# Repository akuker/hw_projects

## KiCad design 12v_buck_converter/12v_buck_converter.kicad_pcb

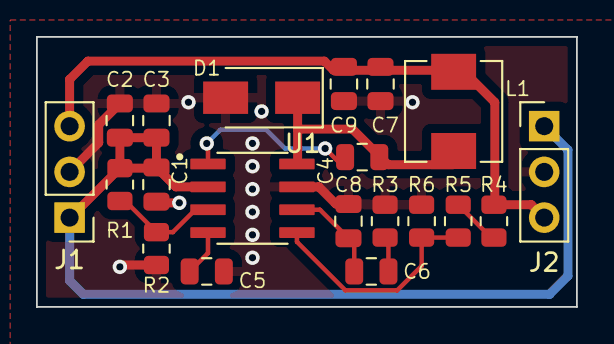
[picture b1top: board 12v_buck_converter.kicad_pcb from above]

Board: 2 copper layers, 30.0 x 15.0 mm, 20 parts (0 on the bottom side), 11 nets.

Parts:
C1, C2: 4.7u; C_0805_2012Metric
C3, C6: 4.7n; C_0805_2012Metric
C4: 0.1u; C_0805_2012Metric
C5: 0.01u; C_0805_2012Metric
C7, C9: 33u; C_0805_2012Metric
C8: 39p; C_0805_2012Metric
D1: B340A; D_SMA
J1, J2: Conn_01x03_Male; PinHeader_1x03_P2.54mm_Vertical
L1: 6.8uH; Sunltech_SLO0530H
R1: 332k; R_0805_2012Metric
R2: 68.1k; R_0805_2012Metric
R3: 49.9k; R_0805_2012Metric
R4: 0; R_0805_2012Metric
R5: 10.2k; R_0805_2012Metric
R6: 3.24k; R_0805_2012Metric
U1: TPS54331DR; SOIC127P599X175-8N

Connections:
+5V: C7.1, C9.1, J1.3, J2.3, L1.2, R4.1
+12V: C1.1, C2.1, C3.1, J1.1, J2.1, R1.1, U1.2 (VIN)
GND: C1.2, C2.2, C3.2, C5.2, C7.2, C8.2, C9.2, D1.2 (A), J1.2, J2.2, R2.2, R3.2, R6.2, U1.7 (GND)
unnamed: C4.1, D1.1 (K), L1.1, U1.8 (PH)
unnamed: C4.2, U1.1 (BOOT)
unnamed: C5.1, U1.4 (SS)
unnamed: C6.1, C8.1, U1.6 (COMP)
unnamed: C6.2, R3.1
unnamed: R1.2, R2.1, U1.3 (EN)
unnamed: R4.2, R5.1
unnamed: R5.2, R6.1, U1.5 (VSENSE)

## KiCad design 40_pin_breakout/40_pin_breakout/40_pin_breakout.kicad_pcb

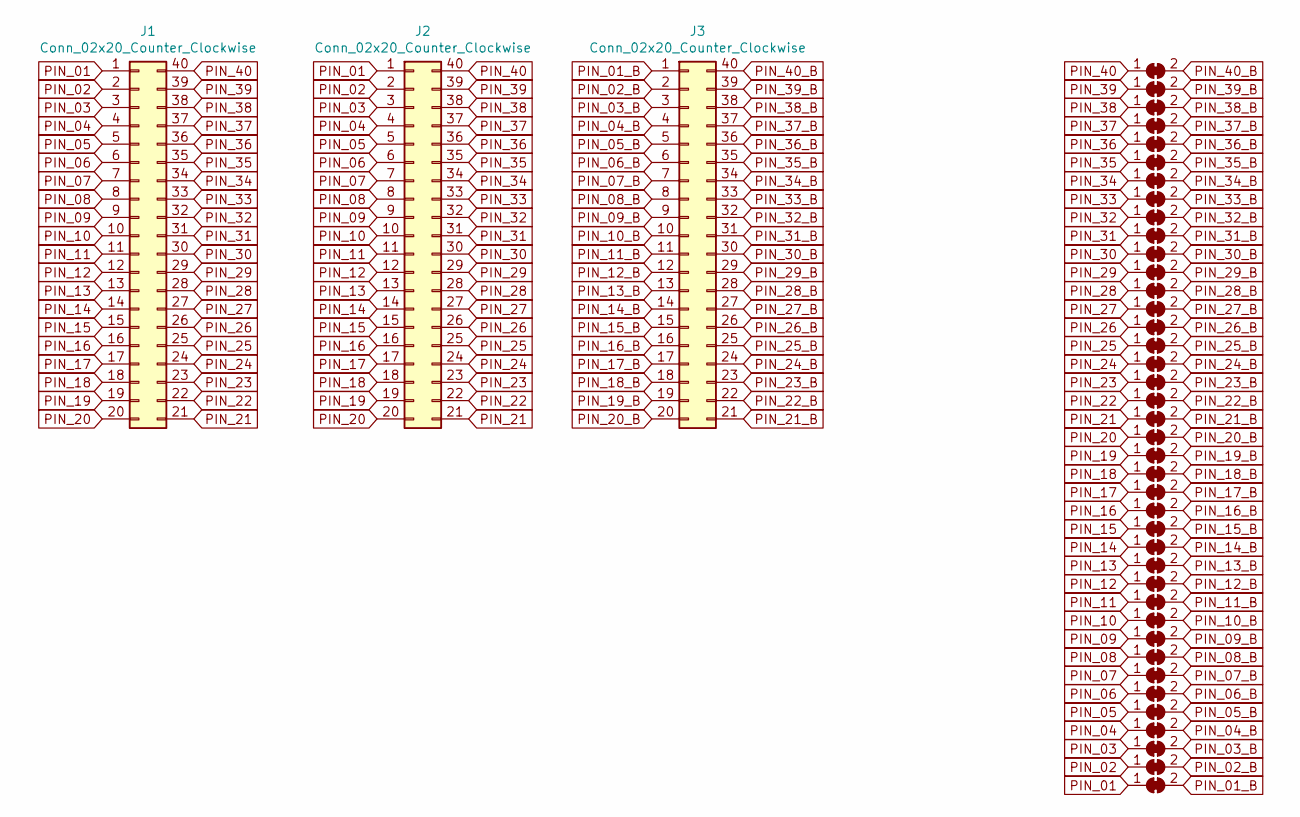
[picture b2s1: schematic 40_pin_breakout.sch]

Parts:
J1, J2, J3: Conn_02x20_Counter_Clockwise; PinHeader_2x20_P2.54mm_Vertical
JP1, JP2, JP3, JP4, JP5, JP6, JP7, JP8, JP9, JP10, JP11, JP12, JP13, JP14, JP15, JP16, JP17, JP18, JP19, JP20, JP21, JP22, JP23, JP24, JP25, JP26, JP27, JP28, JP29, JP30, JP31, JP32, JP33, JP34, JP35, JP36, JP37, JP38, JP39, JP40: SolderJumper_2_Bridged; SolderJumper-2_P1.3mm_Bridged2Bar_Pad1.0x1.5mm

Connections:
PIN_01: J1.1, J2.1, JP40.1 (A)
PIN_01_B: J3.1, JP40.2 (B)
PIN_02: J1.2, J2.2, JP39.1 (A)
PIN_02_B: J3.2, JP39.2 (B)
PIN_03: J1.3, J2.3, JP38.1 (A)
PIN_03_B: J3.3, JP38.2 (B)
PIN_04: J1.4, J2.4, JP37.1 (A)
PIN_04_B: J3.4, JP37.2 (B)
PIN_05: J1.5, J2.5, JP36.1 (A)
PIN_05_B: J3.5, JP36.2 (B)
PIN_06: J1.6, J2.6, JP35.1 (A)
PIN_06_B: J3.6, JP35.2 (B)
PIN_07: J1.7, J2.7, JP34.1 (A)
PIN_07_B: J3.7, JP34.2 (B)
PIN_08: J1.8, J2.8, JP33.1 (A)
PIN_08_B: J3.8, JP33.2 (B)
PIN_09: J1.9, J2.9, JP32.1 (A)
PIN_09_B: J3.9, JP32.2 (B)
PIN_10: J1.10, J2.10, JP31.1 (A)
PIN_10_B: J3.10, JP31.2 (B)
PIN_11: J1.11, J2.11, JP30.1 (A)
PIN_11_B: J3.11, JP30.2 (B)
PIN_12: J1.12, J2.12, JP29.1 (A)
PIN_12_B: J3.12, JP29.2 (B)
PIN_13: J1.13, J2.13, JP28.1 (A)
PIN_13_B: J3.13, JP28.2 (B)
PIN_14: J1.14, J2.14, JP27.1 (A)
PIN_14_B: J3.14, JP27.2 (B)
PIN_15: J1.15, J2.15, JP26.1 (A)
PIN_15_B: J3.15, JP26.2 (B)
PIN_16: J1.16, J2.16, JP25.1 (A)
PIN_16_B: J3.16, JP25.2 (B)
PIN_17: J1.17, J2.17, JP24.1 (A)
PIN_17_B: J3.17, JP24.2 (B)
PIN_18: J1.18, J2.18, JP23.1 (A)
PIN_18_B: J3.18, JP23.2 (B)
PIN_19: J1.19, J2.19, JP22.1 (A)
PIN_19_B: J3.19, JP22.2 (B)
PIN_20: J1.20, J2.20, JP21.1 (A)
PIN_20_B: J3.20, JP21.2 (B)
PIN_21: J1.21, J2.21, JP20.1 (A)
PIN_21_B: J3.21, JP20.2 (B)
PIN_22: J1.22, J2.22, JP19.1 (A)
PIN_22_B: J3.22, JP19.2 (B)
PIN_23: J1.23, J2.23, JP18.1 (A)
PIN_23_B: J3.23, JP18.2 (B)
PIN_24: J1.24, J2.24, JP17.1 (A)
PIN_24_B: J3.24, JP17.2 (B)
PIN_25: J1.25, J2.25, JP16.1 (A)
PIN_25_B: J3.25, JP16.2 (B)
PIN_26: J1.26, J2.26, JP15.1 (A)
PIN_26_B: J3.26, JP15.2 (B)
PIN_27: J1.27, J2.27, JP14.1 (A)
PIN_27_B: J3.27, JP14.2 (B)
PIN_28: J1.28, J2.28, JP13.1 (A)
PIN_28_B: J3.28, JP13.2 (B)
PIN_29: J1.29, J2.29, JP12.1 (A)
PIN_29_B: J3.29, JP12.2 (B)
PIN_30: J1.30, J2.30, JP11.1 (A)
PIN_30_B: J3.30, JP11.2 (B)
PIN_31: J1.31, J2.31, JP10.1 (A)
PIN_31_B: J3.31, JP10.2 (B)
PIN_32: J1.32, J2.32, JP9.1 (A)
PIN_32_B: J3.32, JP9.2 (B)
PIN_33: J1.33, J2.33, JP8.1 (A)
PIN_33_B: J3.33, JP8.2 (B)
PIN_34: J1.34, J2.34, JP7.1 (A)
PIN_34_B: J3.34, JP7.2 (B)
PIN_35: J1.35, J2.35, JP6.1 (A)
PIN_35_B: J3.35, JP6.2 (B)
PIN_36: J1.36, J2.36, JP5.1 (A)
PIN_36_B: J3.36, JP5.2 (B)
PIN_37: J1.37, J2.37, JP4.1 (A)
PIN_37_B: J3.37, JP4.2 (B)
PIN_38: J1.38, J2.38, JP3.1 (A)
PIN_38_B: J3.38, JP3.2 (B)
PIN_39: J1.39, J2.39, JP2.1 (A)
PIN_39_B: J3.39, JP2.2 (B)
PIN_40: J1.40, J2.40, JP1.1 (A)
PIN_40_B: J3.40, JP1.2 (B)

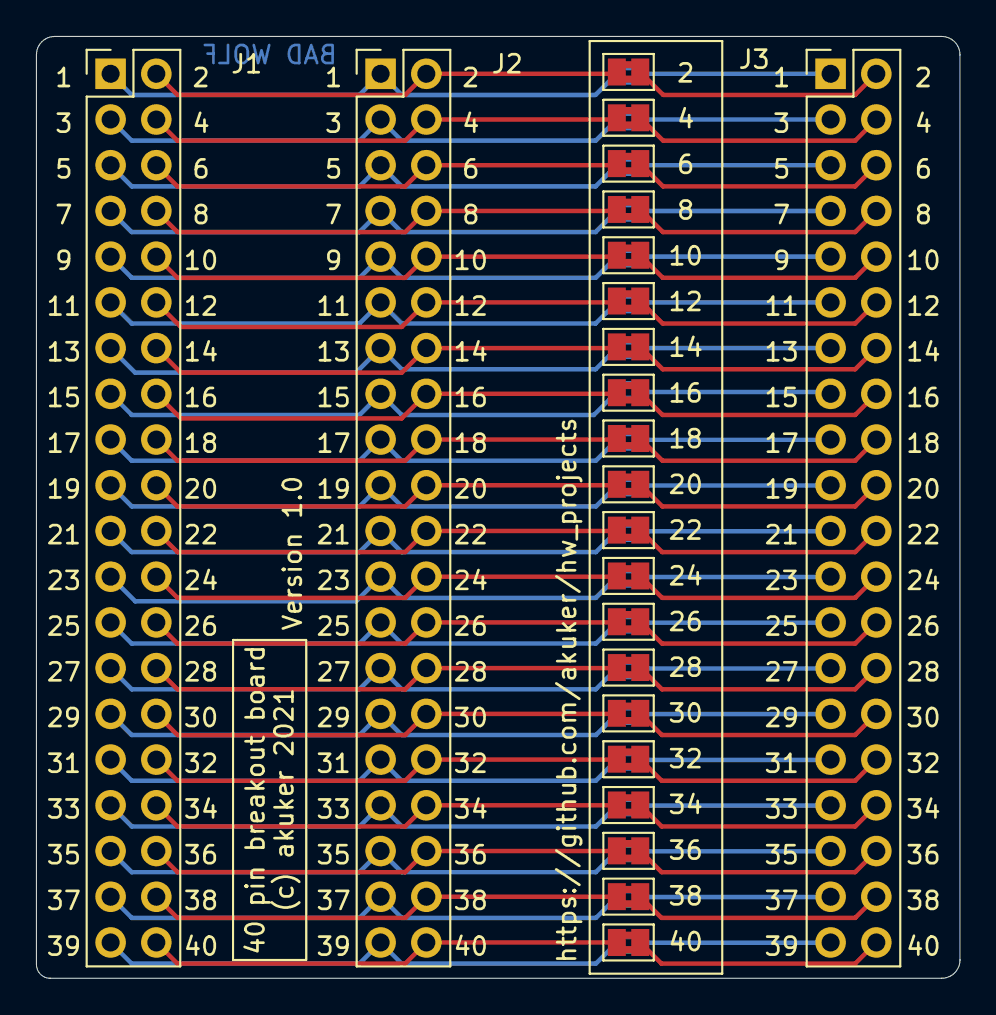
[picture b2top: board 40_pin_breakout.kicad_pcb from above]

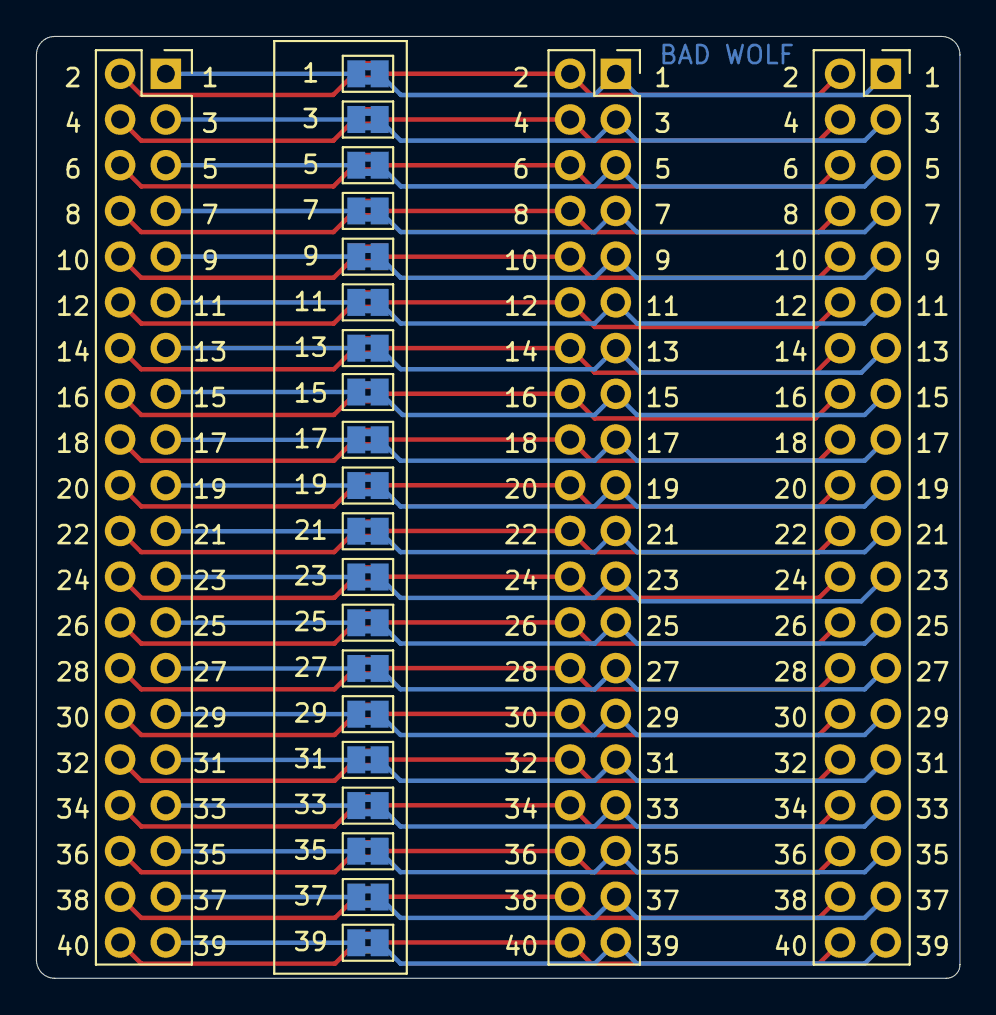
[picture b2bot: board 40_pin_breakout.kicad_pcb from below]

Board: 2 copper layers, 51.3 x 52.3 mm, 43 parts (20 on the bottom side), 80 nets.

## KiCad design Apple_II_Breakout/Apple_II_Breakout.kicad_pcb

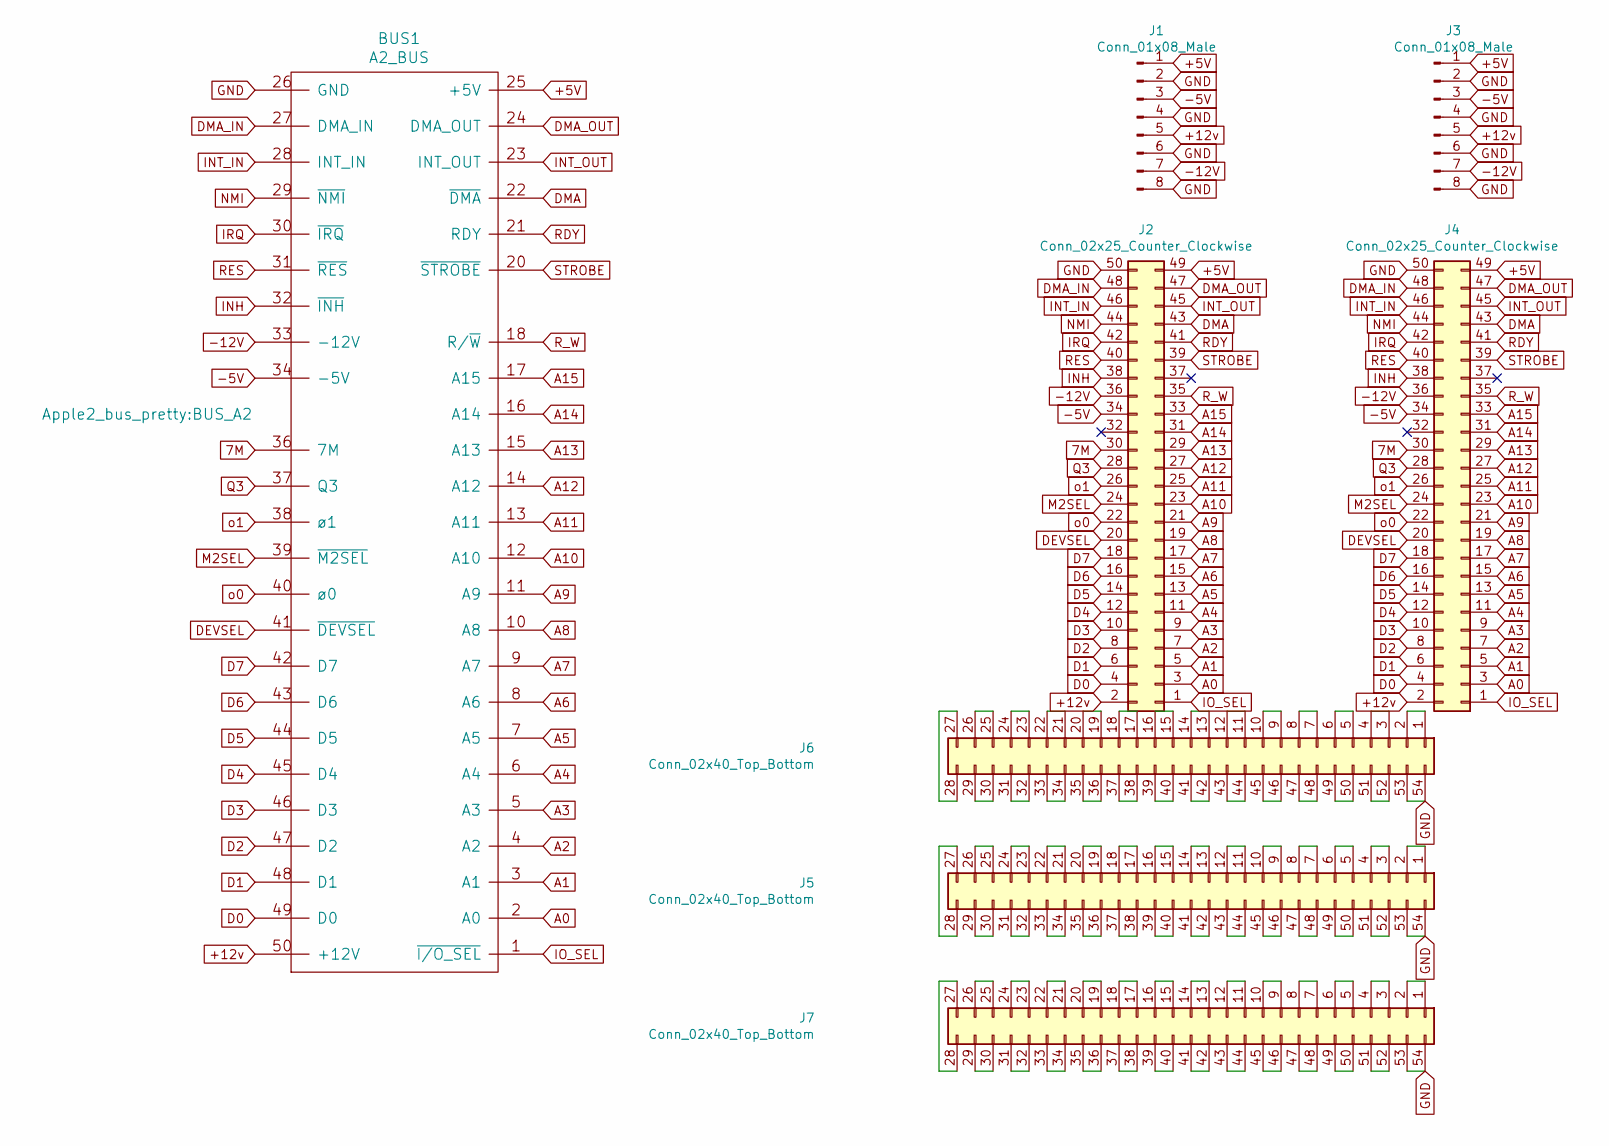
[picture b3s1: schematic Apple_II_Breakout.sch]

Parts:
BUS1: A2_BUS; BUS_A2
J1, J3: Conn_01x08_Male; PinHeader_1x08_P2.54mm_Vertical
J2, J4: Conn_02x25_Counter_Clockwise; PinHeader_2x25_P2.54mm_Vertical
J5, J6, J7: Conn_02x40_Top_Bottom; PinHeader_2x27_P2.54mm_Vertical

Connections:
7M: BUS1.36 (7M), J2.30, J4.30
+5V: BUS1.25 (+5V), J1.1, J2.49, J3.1, J4.49
+12v: BUS1.50 (+12V), J1.5, J2.2, J3.5, J4.2
-5V: BUS1.34 (-5V), J1.3, J2.34, J3.3, J4.34
-12V: BUS1.33 (-12V), J1.7, J2.36, J3.7, J4.36
A0: BUS1.2 (A0), J2.3, J4.3
A1: BUS1.3 (A1), J2.5, J4.5
A2: BUS1.4 (A2), J2.7, J4.7
A3: BUS1.5 (A3), J2.9, J4.9
A4: BUS1.6 (A4), J2.11, J4.11
A5: BUS1.7 (A5), J2.13, J4.13
A6: BUS1.8 (A6), J2.15, J4.15
A7: BUS1.9 (A7), J2.17, J4.17
A8: BUS1.10 (A8), J2.19, J4.19
A9: BUS1.11 (A9), J2.21, J4.21
A10: BUS1.12 (A10), J2.23, J4.23
A11: BUS1.13 (A11), J2.25, J4.25
A12: BUS1.14 (A12), J2.27, J4.27
A13: BUS1.15 (A13), J2.29, J4.29
A14: BUS1.16 (A14), J2.31, J4.31
A15: BUS1.17 (A15), J2.33, J4.33
D0: BUS1.49 (D0), J2.4, J4.4
D1: BUS1.48 (D1), J2.6, J4.6
D2: BUS1.47 (D2), J2.8, J4.8
D3: BUS1.46 (D3), J2.10, J4.10
D4: BUS1.45 (D4), J2.12, J4.12
D5: BUS1.44 (D5), J2.14, J4.14
D6: BUS1.43 (D6), J2.16, J4.16
D7: BUS1.42 (D7), J2.18, J4.18
DEVSEL: BUS1.41 (~DEVSEL), J2.20, J4.20
DMA: BUS1.22 (~DMA), J2.43, J4.43
DMA_IN: BUS1.27 (DMA_IN), J2.48, J4.48
DMA_OUT: BUS1.24 (DMA_OUT), J2.47, J4.47
GND: BUS1.26 (GND), J1.2, J1.4, J1.6, J1.8, J2.50, J3.2, J3.4, J3.6, J3.8, J4.50, J5.53, J5.54, J6.53, J6.54, J7.53, J7.54
INH: BUS1.32 (~INH), J2.38, J4.38
INT_IN: BUS1.28 (INT_IN), J2.46, J4.46
INT_OUT: BUS1.23 (INT_OUT), J2.45, J4.45
IO_SEL: BUS1.1 (~I/O_SEL), J2.1, J4.1
IRQ: BUS1.30 (~IRQ), J2.42, J4.42
M2SEL: BUS1.39 (~M2SEL), J2.24, J4.24
NMI: BUS1.29 (~NMI), J2.44, J4.44
unnamed: J5.1, J5.2
unnamed: J5.3, J5.4
unnamed: J5.5, J5.6
unnamed: J5.7, J5.8
unnamed: J5.9, J5.10
unnamed: J5.11, J5.12
unnamed: J5.13, J5.14
unnamed: J5.15, J5.16
unnamed: J5.17, J5.18
unnamed: J5.19, J5.20
unnamed: J5.21, J5.22
unnamed: J5.23, J5.24
unnamed: J5.25, J5.26
unnamed: J5.27, J5.28
unnamed: J5.29, J5.30
unnamed: J5.31, J5.32
unnamed: J5.33, J5.34
unnamed: J5.35, J5.36
unnamed: J5.37, J5.38
unnamed: J5.39, J5.40
unnamed: J5.41, J5.42
unnamed: J5.43, J5.44
unnamed: J5.45, J5.46
unnamed: J5.47, J5.48
unnamed: J5.49, J5.50
unnamed: J5.51, J5.52
unnamed: J6.1, J6.2
unnamed: J6.3, J6.4
unnamed: J6.5, J6.6
unnamed: J6.7, J6.8
unnamed: J6.9, J6.10
unnamed: J6.11, J6.12
unnamed: J6.13, J6.14
unnamed: J6.15, J6.16
unnamed: J6.17, J6.18
unnamed: J6.19, J6.20
unnamed: J6.21, J6.22
unnamed: J6.23, J6.24
unnamed: J6.25, J6.26
unnamed: J6.27, J6.28
unnamed: J6.29, J6.30
unnamed: J6.31, J6.32
unnamed: J6.33, J6.34
unnamed: J6.35, J6.36
unnamed: J6.37, J6.38
unnamed: J6.39, J6.40
unnamed: J6.41, J6.42
unnamed: J6.43, J6.44
unnamed: J6.45, J6.46
unnamed: J6.47, J6.48
unnamed: J6.49, J6.50
unnamed: J6.51, J6.52
unnamed: J7.1, J7.2
unnamed: J7.3, J7.4
unnamed: J7.5, J7.6
unnamed: J7.7, J7.8
unnamed: J7.9, J7.10
unnamed: J7.11, J7.12
unnamed: J7.13, J7.14
unnamed: J7.15, J7.16
unnamed: J7.17, J7.18
unnamed: J7.19, J7.20
unnamed: J7.21, J7.22
unnamed: J7.23, J7.24
unnamed: J7.25, J7.26
unnamed: J7.27, J7.28
unnamed: J7.29, J7.30
unnamed: J7.31, J7.32
unnamed: J7.33, J7.34
unnamed: J7.35, J7.36
unnamed: J7.37, J7.38
unnamed: J7.39, J7.40
unnamed: J7.41, J7.42
unnamed: J7.43, J7.44
unnamed: J7.45, J7.46
unnamed: J7.47, J7.48
unnamed: J7.49, J7.50
unnamed: J7.51, J7.52
Q3: BUS1.37 (Q3), J2.28, J4.28
RDY: BUS1.21 (RDY), J2.41, J4.41
RES: BUS1.31 (~RES), J2.40, J4.40
R_W: BUS1.18 (R/~W), J2.35, J4.35
STROBE: BUS1.20 (~STROBE), J2.39, J4.39
o0: BUS1.40 (ø0), J2.22, J4.22
o1: BUS1.38 (ø1), J2.26, J4.26

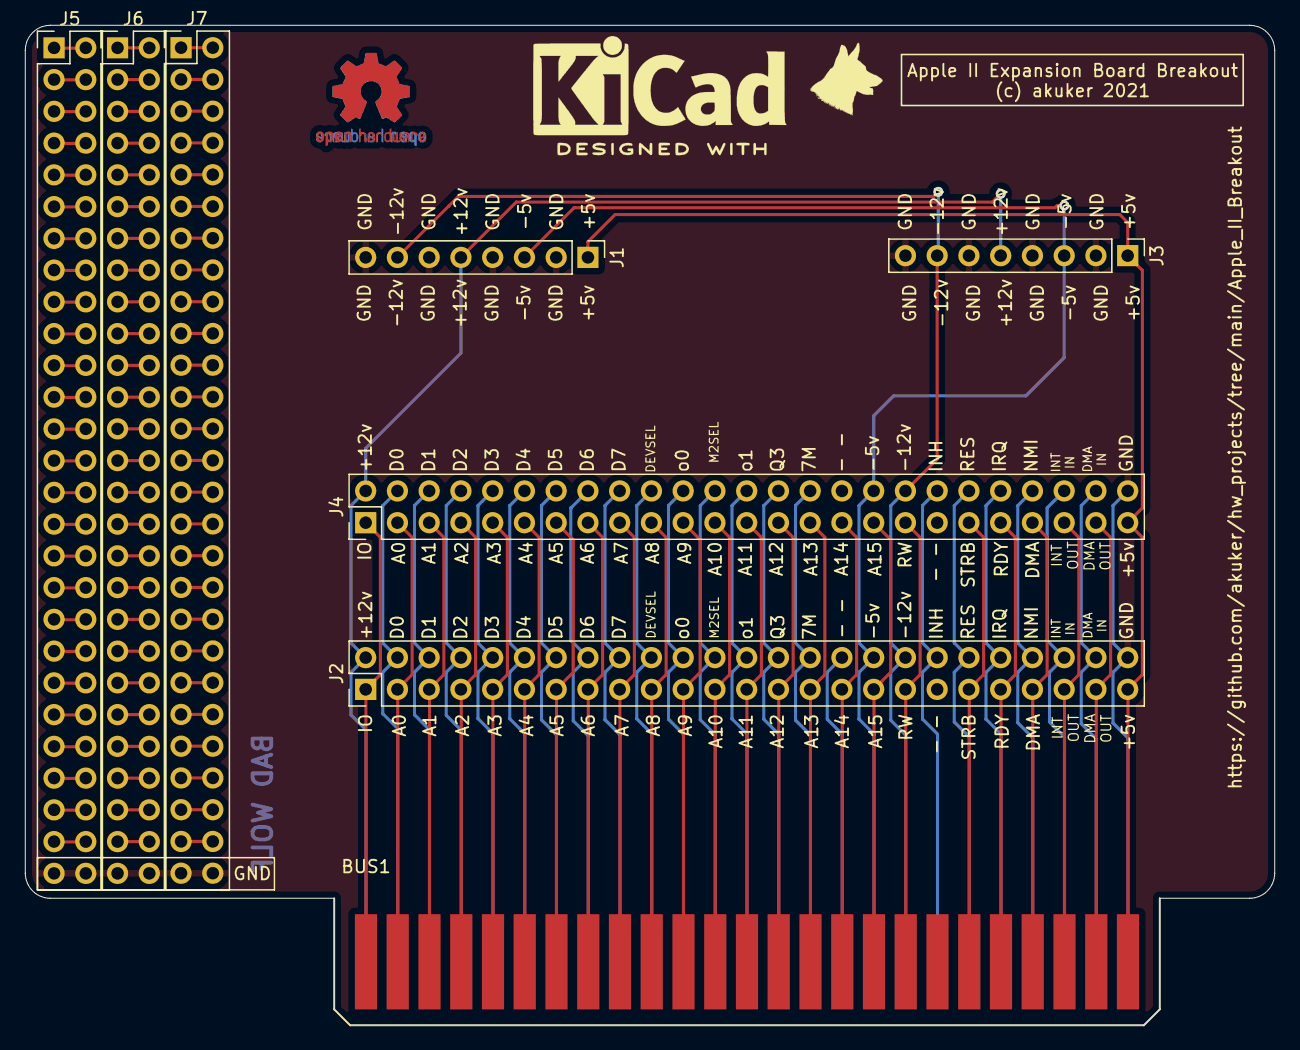
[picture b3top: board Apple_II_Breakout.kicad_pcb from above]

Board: 2 copper layers, 99.9 x 80.0 mm, 8 parts (0 on the bottom side), 126 nets.

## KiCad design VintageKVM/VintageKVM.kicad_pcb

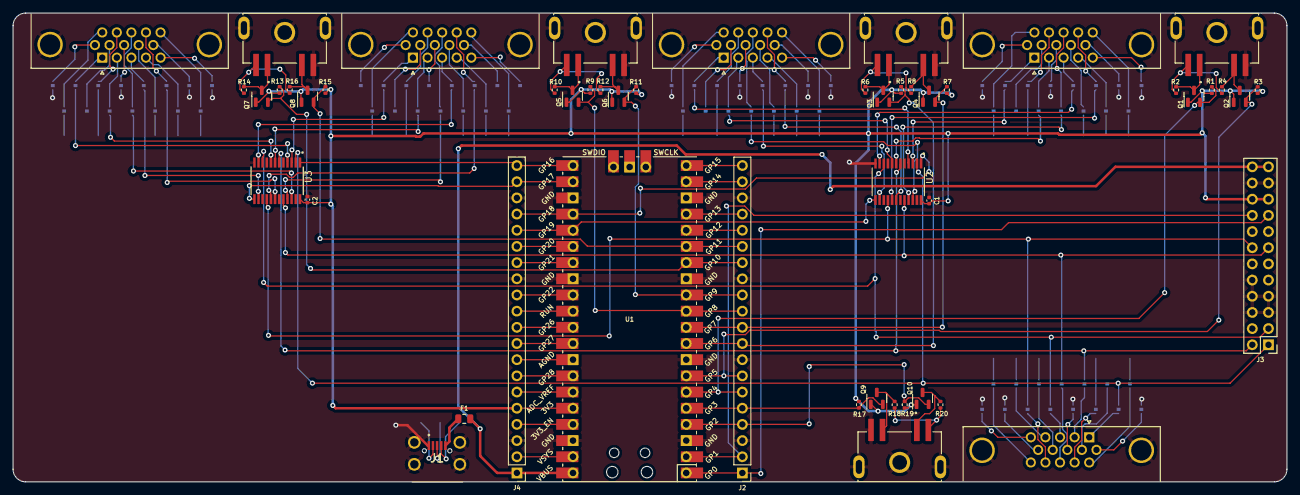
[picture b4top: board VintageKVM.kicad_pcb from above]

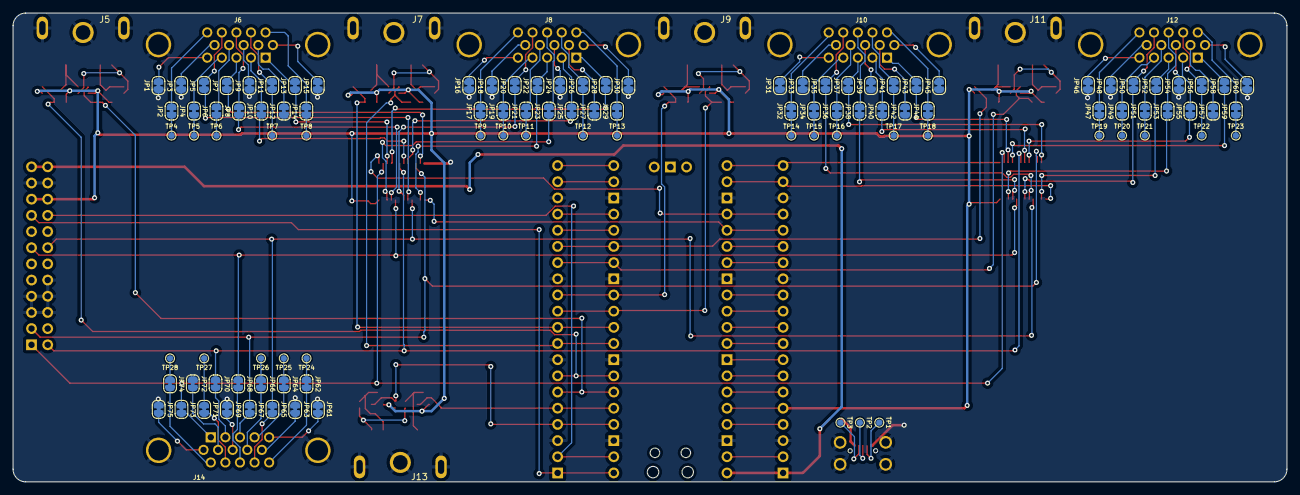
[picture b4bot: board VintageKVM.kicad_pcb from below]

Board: 2 copper layers, 200.0 x 73.6 mm, 153 parts (103 on the bottom side), 178 nets.

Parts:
C1, C2: 100nF; C_0402_1005Metric
F1: Polyfuse; Fuse_0805_2012Metric
J1: Micro USB; U254051N4BH806
J2, J4: Conn_01x20_Pin; PinHeader_1x20_P2.54mm_Vertical
J3: Conn_02x10_Odd_Even; PinHeader_2x12_P2.54mm_Vertical
J5, J7, J9, J11, J13: CUI_MD2-40ST-SMT
J6, J8, J10, J12, J14: DE15_Receptacle_HighDensity_MountingHoles; DSUB-15-HD_Female_Horizontal_P2.29x1.98mm_EdgePinOffset3.03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
JP1, JP2, JP3, JP4, JP5, JP6, JP7, JP8, JP9, JP10, JP11, JP12, JP13, JP14, JP15, JP16, JP17, JP18, JP19, JP20, JP21, JP22, JP23, JP24, JP25, JP26, JP27, JP28, JP29, JP30, JP31, JP32, JP33, JP34, JP35, JP36, JP37, JP38, JP39, JP40, JP41, JP42, JP43, JP44, JP45, JP46, JP47, JP48, JP49, JP50, JP51, JP52, JP53, JP54, JP55, JP56, JP57, JP58, JP59, JP60, JP61, JP62, JP63, JP64, JP65, JP66, JP67, JP68, JP69, JP70, JP71, JP72, JP73, JP74, JP75: SolderJumper_2_Bridged; SolderJumper-2_P1.3mm_Bridged_RoundedPad1.0x1.5mm
Q1, Q2, Q3, Q4, Q5, Q6, Q7, Q8, Q9, Q10: BSS138; SOT-23
R1, R2, R3, R4, R5, R6, R7, R8, R9, R10, R11, R12, R13, R14, R15, R16, R17, R18, R19, R20: 10k; R_0402_1005Metric
TP1, TP2, TP3: TestPoint_Pad_D1.0mm
TP4, TP5, TP6, TP7, TP8, TP9, TP10, TP11, TP12, TP13, TP14, TP15, TP16, TP17, TP18, TP19, TP20, TP21, TP22, TP23, TP24, TP25, TP26, TP27, TP28: TestPoint_Small; TestPoint_Pad_D1.0mm
U1: Pico; RPi_Pico_SMD_TH
U2, U3: TS5V522CPWR; SOP65P640X120-24N

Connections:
3v3_EN: J4.4, U1.37 (3V3_EN)
+3V3: C1.1, C2.1, J3.19, J3.20, J4.5, Q1.1 (G), Q2.1 (G), Q3.1 (G), Q4.1 (G), Q5.1 (G), Q6.1 (G), Q7.1 (G), Q8.1 (G), Q9.1 (G), Q10.1 (G), R1.1, R3.1, R5.1, R7.1, R9.1, R11.1, R13.1, R15.1, R17.1, R19.1, U1.36 (3V3), U2.24 (VCC), U3.24 (VCC)
/Control Port/ADB_EXT_5v: J13.3, R18.1, R20.1
/Control Port/ADB_EXT_DATA: J13.1, Q10.3 (D), R20.2
/Control Port/ADB_EXT_PWR_ON: J13.2, Q9.3 (D), R18.2
/Input Port 1/ADB_EXT_5v: J5.3, R2.1, R4.1
/Input Port 1/ADB_EXT_DATA: J5.1, Q1.3 (D), R2.2
/Input Port 1/ADB_EXT_PWR_ON: J5.2, Q2.3 (D), R4.2
/Input Port 2/ADB_EXT_5v: J7.3, R6.1, R8.1
/Input Port 2/ADB_EXT_DATA: J7.1, Q3.3 (D), R6.2
/Input Port 2/ADB_EXT_PWR_ON: J7.2, Q4.3 (D), R8.2
/Input Port 3/ADB_EXT_5v: J9.3, R10.1, R12.1
/Input Port 3/ADB_EXT_DATA: J9.1, Q5.3 (D), R10.2
/Input Port 3/ADB_EXT_PWR_ON: J9.2, Q6.3 (D), R12.2
/Input Port 4/ADB_EXT_5v: J11.3, R14.1, R16.1
/Input Port 4/ADB_EXT_DATA: J11.1, Q7.3 (D), R14.2
/Input Port 4/ADB_EXT_PWR_ON: J11.2, Q8.3 (D), R16.2
ADC_VREF: J4.6, U1.35 (ADC_VREF)
AGND: J4.8, U1.33 (AGND)
CTRL_PORT_ADB_DATA: J2.5, Q9.2 (S), R17.2, U1.5 (GPIO3)
CTRL_PORT_ADB_PWR_ON: J2.4, Q10.2 (S), R19.2, U1.4 (GPIO2)
CTRL_PORT_BLUE: J3.3, JP67.1 (A), U2.10 (AB), U3.10 (AB)
CTRL_PORT_GREEN: J3.2, JP70.1 (A), U2.6 (AG), U3.6 (AG)
CTRL_PORT_HSYNC: J3.13, JP68.1 (A), U2.20 (ASCL), U3.20 (ASCL)
CTRL_PORT_RED: J3.1, JP73.1 (A), U2.2 (AR), U3.2 (AR)
CTRL_PORT_VSYNC: J3.14, JP65.1 (A), U2.16 (ASCA), U3.16 (ASCA)
GND: C1.2, C2.2, J1.1, J1.MH1, J1.MH2, J1.MH3, J1.MH4, J2.3, J2.8, J2.13, J2.18, J3.5, J3.6, J3.7, J3.8, J3.10, J3.21, J3.22, J4.3, J4.13, J4.18, J5.4, J5.S1 (SHIELD), J5.S2 (SHIELD), J5.S3 (SHIELD), J6.0, J7.4, J7.S1 (SHIELD), J7.S2 (SHIELD), J7.S3 (SHIELD), J8.0, J9.4, J9.S1 (SHIELD), J9.S2 (SHIELD), J9.S3 (SHIELD), J10.0, J11.4, J11.S1 (SHIELD), J11.S2 (SHIELD), J11.S3 (SHIELD), J12.0, J13.4, J13.S1 (SHIELD), J13.S2 (SHIELD), J13.S3 (SHIELD), J14.0, JP1.1 (A), JP3.1 (A), JP9.1 (A), JP12.1 (A), JP15.1 (A), JP16.1 (A), JP18.1 (A), JP24.1 (A), JP27.1 (A), JP30.1 (A), JP31.1 (A), JP33.1 (A), JP39.1 (A), JP42.1 (A), JP45.1 (A), JP46.1 (A), JP48.1 (A), JP54.1 (A), JP57.1 (A), JP60.1 (A), JP61.1 (A), JP63.1 (A), JP69.1 (A), JP72.1 (A), JP75.1 (A), U1.3 (GND), U1.8 (GND), U1.13 (GND), U1.18 (GND), U1.23 (GND), U1.28 (GND), U1.38 (GND), U2.12 (GND), U3.12 (GND)
GPIO14: J2.19, U1.19 (GPIO14)
GPIO15: J2.20, U1.20 (GPIO15)
GPIO20: J4.15, U1.26 (GPIO20)
GPIO21: J4.14, U1.27 (GPIO21)
GPIO22: J4.12, U1.29 (GPIO22)
GPIO26: J4.10, U1.31 (GPIO26_ADC0)
GPIO27: J4.9, U1.32 (GPIO27_ADC1)
GPIO28: J4.7, U1.34 (GPIO28_ADC2)
I2C0_SCL: J2.2, J3.18, U1.2 (GPIO1)
I2C0_SDA: J2.1, J3.17, U1.1 (GPIO0)
unnamed: F1.1, J1.5
unnamed: J1.2, TP1.1
unnamed: J1.3, TP2.1
unnamed: J1.4, TP3.1
unnamed: J6.5, JP1.2 (B)
unnamed: JP2.1 (A), TP4.1
unnamed: J6.15, JP2.2 (B)
unnamed: J6.10, JP3.2 (B)
unnamed: JP4.1 (A), TP5.1
unnamed: J6.4, JP4.2 (B)
unnamed: J6.14, JP5.2 (B)
unnamed: JP6.1 (A), TP6.1
unnamed: J6.9, JP6.2 (B)
unnamed: J6.3, JP7.2 (B)
unnamed: J6.13, JP8.2 (B)
unnamed: J6.8, JP9.2 (B)
unnamed: J6.2, JP10.2 (B)
unnamed: JP11.1 (A), TP7.1
unnamed: J6.12, JP11.2 (B)
unnamed: J6.7, JP12.2 (B)
unnamed: J6.1, JP13.2 (B)
unnamed: JP14.1 (A), TP8.1
unnamed: J6.11, JP14.2 (B)
unnamed: J6.6, JP15.2 (B)
unnamed: J8.5, JP16.2 (B)
unnamed: JP17.1 (A), TP9.1
unnamed: J8.15, JP17.2 (B)
unnamed: J8.10, JP18.2 (B)
unnamed: JP19.1 (A), TP10.1
unnamed: J8.4, JP19.2 (B)
unnamed: J8.14, JP20.2 (B)
unnamed: JP21.1 (A), TP11.1
unnamed: J8.9, JP21.2 (B)
unnamed: J8.3, JP22.2 (B)
unnamed: J8.13, JP23.2 (B)
unnamed: J8.8, JP24.2 (B)
unnamed: J8.2, JP25.2 (B)
unnamed: JP26.1 (A), TP12.1
unnamed: J8.12, JP26.2 (B)
unnamed: J8.7, JP27.2 (B)
unnamed: J8.1, JP28.2 (B)
unnamed: JP29.1 (A), TP13.1
unnamed: J8.11, JP29.2 (B)
unnamed: J8.6, JP30.2 (B)
unnamed: J10.5, JP31.2 (B)
unnamed: JP32.1 (A), TP14.1
unnamed: J10.15, JP32.2 (B)
unnamed: J10.10, JP33.2 (B)
unnamed: JP34.1 (A), TP15.1
unnamed: J10.4, JP34.2 (B)
unnamed: J10.14, JP35.2 (B)
unnamed: JP36.1 (A), TP16.1
unnamed: J10.9, JP36.2 (B)
unnamed: J10.3, JP37.2 (B)
unnamed: J10.13, JP38.2 (B)
unnamed: J10.8, JP39.2 (B)
unnamed: J10.2, JP40.2 (B)
unnamed: JP41.1 (A), TP17.1
unnamed: J10.12, JP41.2 (B)
unnamed: J10.7, JP42.2 (B)
unnamed: J10.1, JP43.2 (B)
unnamed: JP44.1 (A), TP18.1
unnamed: J10.11, JP44.2 (B)
unnamed: J10.6, JP45.2 (B)
unnamed: J12.5, JP46.2 (B)
unnamed: JP47.1 (A), TP19.1
unnamed: J12.15, JP47.2 (B)
unnamed: J12.10, JP48.2 (B)
unnamed: JP49.1 (A), TP20.1
unnamed: J12.4, JP49.2 (B)
unnamed: J12.14, JP50.2 (B)
unnamed: JP51.1 (A), TP21.1
unnamed: J12.9, JP51.2 (B)
unnamed: J12.3, JP52.2 (B)
unnamed: J12.13, JP53.2 (B)
unnamed: J12.8, JP54.2 (B)
unnamed: J12.2, JP55.2 (B)
unnamed: JP56.1 (A), TP22.1
unnamed: J12.12, JP56.2 (B)
unnamed: J12.7, JP57.2 (B)
unnamed: J12.1, JP58.2 (B)
unnamed: JP59.1 (A), TP23.1
unnamed: J12.11, JP59.2 (B)
unnamed: J12.6, JP60.2 (B)
unnamed: J14.5, JP61.2 (B)
unnamed: JP62.1 (A), TP24.1
unnamed: J14.15, JP62.2 (B)
unnamed: J14.10, JP63.2 (B)
unnamed: JP64.1 (A), TP25.1
unnamed: J14.4, JP64.2 (B)
unnamed: J14.14, JP65.2 (B)
unnamed: JP66.1 (A), TP26.1
unnamed: J14.9, JP66.2 (B)
unnamed: J14.3, JP67.2 (B)
unnamed: J14.13, JP68.2 (B)
unnamed: J14.8, JP69.2 (B)
unnamed: J14.2, JP70.2 (B)
unnamed: JP71.1 (A), TP27.1
unnamed: J14.12, JP71.2 (B)
unnamed: J14.7, JP72.2 (B)
unnamed: J14.1, JP73.2 (B)
unnamed: JP74.1 (A), TP28.1
unnamed: J14.11, JP74.2 (B)
unnamed: J14.6, JP75.2 (B)
OE_U1: J4.17, U1.24 (GPIO18), U2.1 (OE)
OE_U2: J4.20, U1.21 (GPIO16), U3.1 (OE)
PORT_1_ADB_DATA: J2.7, Q2.2 (S), R3.2, U1.7 (GPIO5)
PORT_1_ADB_PWR_ON: J2.6, Q1.2 (S), R1.2, U1.6 (GPIO4)
PORT_1_BLUE: JP7.1 (A), U2.11 (1B)
PORT_1_GREEN: JP10.1 (A), U2.7 (1G)
PORT_1_HSYNC: JP8.1 (A), U2.21 (1SCL)
PORT_1_RED: JP13.1 (A), U2.3 (1R)
PORT_1_VSYNC: JP5.1 (A), U2.17 (1SCA)
PORT_2_ADB_DATA: J2.10, Q4.2 (S), R7.2, U1.10 (GPIO7)
PORT_2_ADB_PWR_ON: J2.9, Q3.2 (S), R5.2, U1.9 (GPIO6)
PORT_2_BLUE: JP22.1 (A), U2.14 (2B)
PORT_2_GREEN: JP25.1 (A), U2.8 (2G)
PORT_2_HSYNC: JP23.1 (A), U2.22 (2SCL)
PORT_2_RED: JP28.1 (A), U2.4 (2R)
PORT_2_VSYNC: JP20.1 (A), U2.18 (2SCA)
PORT_3_ADB_DATA: J2.12, Q6.2 (S), R11.2, U1.12 (GPIO9)
PORT_3_ADB_PWR_ON: J2.11, Q5.2 (S), R9.2, U1.11 (GPIO8)
PORT_3_BLUE: JP37.1 (A), U3.11 (1B)
PORT_3_GREEN: JP40.1 (A), U3.7 (1G)
PORT_3_HSYNC: JP38.1 (A), U3.21 (1SCL)
PORT_3_RED: JP43.1 (A), U3.3 (1R)
PORT_3_VSYNC: JP35.1 (A), U3.17 (1SCA)
PORT_4_ADB_DATA: J2.15, Q8.2 (S), R15.2, U1.15 (GPIO11)
PORT_4_ADB_PWR_ON: J2.14, Q7.2 (S), R13.2, U1.14 (GPIO10)
PORT_4_BLUE: JP52.1 (A), U3.14 (2B)
PORT_4_GREEN: JP55.1 (A), U3.8 (2G)
PORT_4_HSYNC: JP53.1 (A), U3.22 (2SCL)
PORT_4_RED: JP58.1 (A), U3.4 (2R)
PORT_4_VSYNC: JP50.1 (A), U3.18 (2SCA)
RUN: J4.11, U1.30 (RUN)
SEL_U1: J4.16, U1.25 (GPIO19), U2.13 (SEL)
SEL_U2: J4.19, U1.22 (GPIO17), U3.13 (SEL)
UART0_RX: J2.17, U1.17 (GPIO13)
UART0_TX: J2.16, U1.16 (GPIO12)
VBUS: F1.2, J3.23, J3.24, J4.1, U1.40 (VBUS)
VSYS: J4.2, U1.39 (VSYS)

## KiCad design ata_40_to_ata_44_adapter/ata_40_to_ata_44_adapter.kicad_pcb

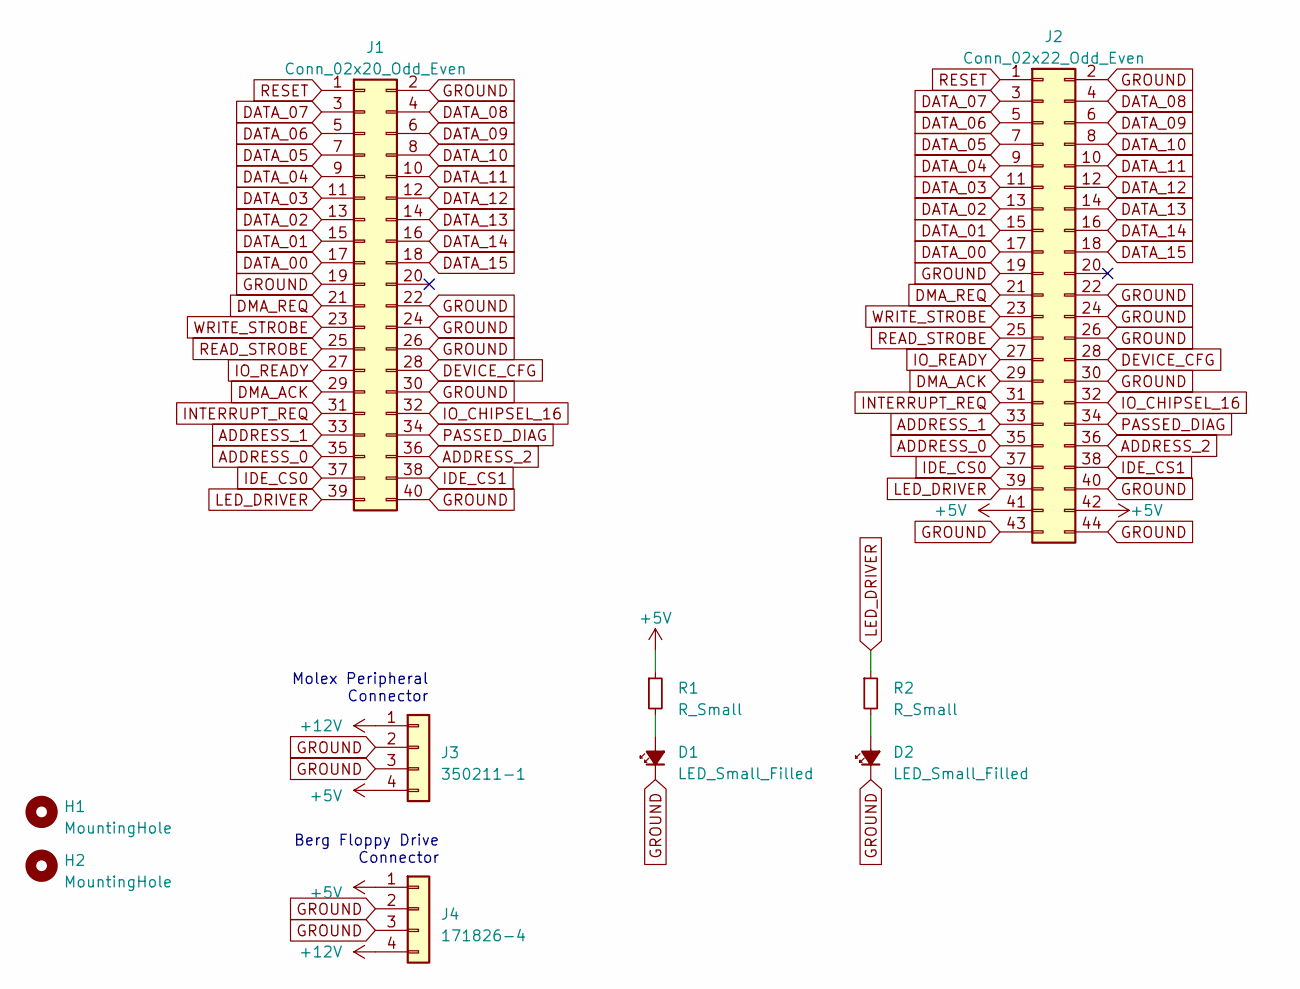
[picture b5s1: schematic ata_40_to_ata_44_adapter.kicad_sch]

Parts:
D1, D2: LED_Small_Filled; LED_0805_2012Metric_Pad1.15x1.40mm_HandSolder
H1, H2: MountingHole; MountingHole_2.7mm_M2.5
J1: Conn_02x20_Odd_Even; PinHeader_2x20_P2.54mm_Vertical
J2: Conn_02x22_Odd_Even; PinHeader_2x22_P2.00mm_Vertical
J3: 350211-1; TE_MATE-N-LOK_350211-1_1x04_P5.08mm_Vertical
J4: 171826-4; TE_171826-4
R1, R2: R_Small; R_0603_1608Metric_Pad0.98x0.95mm_HandSolder

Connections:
+5V: J2.41, J2.42, J3.4, J4.1, R1.1
+12V: J3.1, J4.4
ADDRESS_0: J1.35, J2.35
ADDRESS_1: J1.33, J2.33
ADDRESS_2: J1.36, J2.36
DATA_00: J1.17, J2.17
DATA_01: J1.15, J2.15
DATA_02: J1.13, J2.13
DATA_03: J1.11, J2.11
DATA_04: J1.9, J2.9
DATA_05: J1.7, J2.7
DATA_06: J1.5, J2.5
DATA_07: J1.3, J2.3
DATA_08: J1.4, J2.4
DATA_09: J1.6, J2.6
DATA_10: J1.8, J2.8
DATA_11: J1.10, J2.10
DATA_12: J1.12, J2.12
DATA_13: J1.14, J2.14
DATA_14: J1.16, J2.16
DATA_15: J1.18, J2.18
DEVICE_CFG: J1.28, J2.28
DMA_ACK: J1.29, J2.29
DMA_REQ: J1.21, J2.21
GROUND: D1.1 (K), D2.1 (K), J1.2, J1.19, J1.22, J1.24, J1.26, J1.30, J1.40, J2.2, J2.19, J2.22, J2.24, J2.26, J2.30, J2.40, J2.43, J2.44, J3.2, J3.3, J4.2, J4.3
IDE_CS0: J1.37, J2.37
IDE_CS1: J1.38, J2.38
INTERRUPT_REQ: J1.31, J2.31
IO_CHIPSEL_16: J1.32, J2.32
IO_READY: J1.27, J2.27
LED_DRIVER: J1.39, J2.39, R2.1
unnamed: D1.2 (A), R1.2
unnamed: D2.2 (A), R2.2
PASSED_DIAG: J1.34, J2.34
READ_STROBE: J1.25, J2.25
RESET: J1.1, J2.1
WRITE_STROBE: J1.23, J2.23

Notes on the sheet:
Molex Peripheral Connector
Berg Floppy Drive Connector

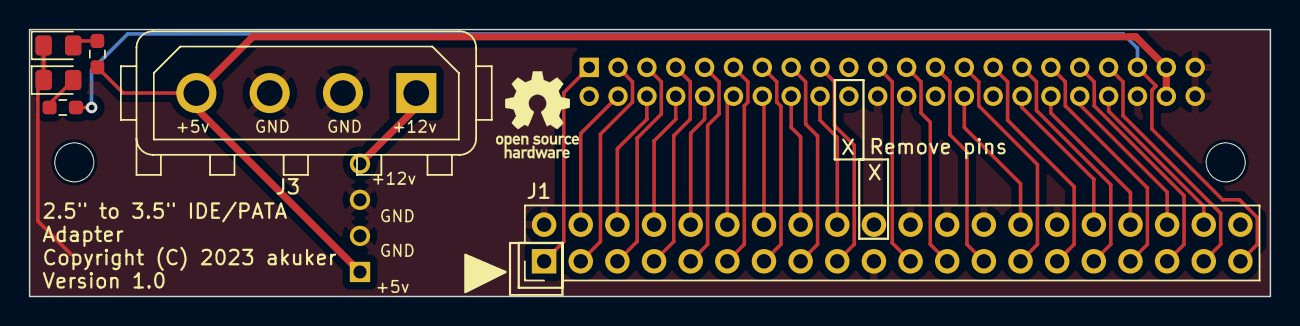
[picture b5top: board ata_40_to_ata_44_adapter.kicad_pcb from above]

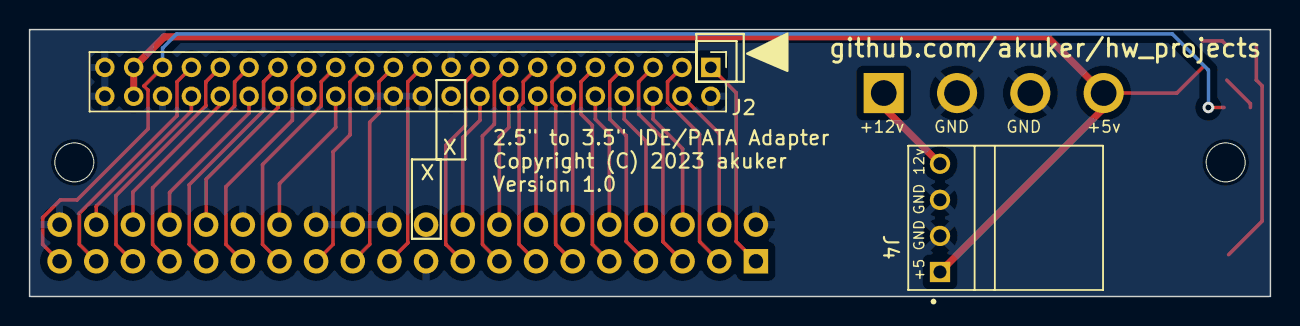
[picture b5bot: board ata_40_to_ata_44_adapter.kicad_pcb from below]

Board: 2 copper layers, 86.0 x 18.5 mm, 10 parts (2 on the bottom side), 37 nets.

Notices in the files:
ata_40_to_ata_44_adapter/ata_40_to_ata_44_adapter.kicad_pcb:
Copyright (C) 2023 akuker
